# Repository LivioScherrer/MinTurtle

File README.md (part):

# EduBot V2

Firmware fuer einen Educational-Roboter auf **Seeed XIAO ESP32S3** mit zwei
NEMA8-Steppern (TMC2209), Farbsensor (TCS34725), Distanzsensor (VL53L0X),
NeoPixel-Ring, BLE-Steuerung und ESP-NOW-Multiplayer.

Zielgruppe der Web-UI ist Grundschule - alle Spiele laufen ueber Bloecke
(Wiederhole, Fahre, Drehe, Warte, Lies Farbe), die per Scratch-Logik
zusammengeklickt werden.

---

## Bauen und Flashen

```bash
pio run                 # kompilieren
pio run -t upload       # auf den Roboter flashen (COM11 in platformio.ini)
pio device monitor      # Serial-Log (115200 baud)
```

Ziel: `seeed_xiao_esp32s3`, Flash 3.3 MB (Stand 2026-10-10: 43,4 % belegt), RAM
327 KB (Stand 2026-10-10: 20,9 % belegt).

Zwei Web-Seiten, beide Single File, kein Build-Schritt. Sie sprechen denselben
BLE-Dienst an und werden direkt aus dem Browser geöffnet (Chromium-Browser
nötig, Web Bluetooth).

> **Achtung beim Verteilen:** `Edu_V2.html` ist keine Einzeldatei mehr. Die
> Schrift **Nunito** liegt selbst gehostet im Ordner `fonts/` daneben
> (2 × `.woff2` + `OFL-Nunito.txt`), damit alle Geräte — auch offline — genau
> gleich aussehen. Wird nur die `.html` kopiert, fällt die Seite still auf
> Comic Sans & Co. zurück. **Immer den ganzen Ordner kopieren.**

| Datei | Für wen | Inhalt |
|---|---|---|
| **`Edu_V2.html`** | **Schüler** | Alle Spiele, Freifahren, Code-Bausteine, Lernkarte. **Keine Diagnose**, keine Fehlermeldungen über unbekannte Befehle. |
| **`Edu_V2_dev.html`** | Entwickler | Kleine Konsole: Protokoll jeder gesendeten und empfangenen Zeile, geparste Werte (TMC, Geometrie, Tempo, Distanz, Freifahren-Kette), freier Befehlseingabe. |

Warum das getrennt ist: `handleCommand()` protokolliert jeden Befehl mit
`Serial.printf("[CMD] %s\n", …)`, und die Firmware antwortet auf Unbekanntes
mit `UNKNOWN:<befehl>`. Auf der Schülerseite wird das **nicht** angezeigt —
für ein Kind ist „Unbekannter Befehl: PROG:OLDRUN" eine tote Fehlermeldung, an
der es nichts zu tun hat, während der Roboter völlig normal läuft. Wer sehen
will, was wirklich ankommt, öffnet die Entwicklerseite.

> **Ein `UNKNOWN:` im Protokoll bedeutet fast immer:** der Browser hat eine
> **alte Kopie** der Web-Seite gecacht und sendet Befehle, die die aktuelle
> Firmware nicht mehr kennt. Abhilfe: Seite neu laden (Strg+F5). Die
> Entwicklerseite zeigt dann sofort, welcher Befehl es ist.

Beide Seiten brauchen die gleichen BLE-UUIDs (siehe `BLEManager.cpp` und den
Kopf beider HTML-Dateien).

---

## Hardware / Verdrahtung

### Motoren (TMC2209, STEP/DIR + UART)

Beide Treiber hängen an einem **gemeinsamen Single-Wire-UART-Bus**.
VIO = 3V3, VM = Motorspannung (ohne VM antwortet der Treiber nicht).

> **Diese Tabelle ist die am Fahrroboter geprüfte IST-Verdrahtung (2026-09).**
> Sie stimmt mit `src/Motor.h` überein. Eine frühere Fassung dieses README
> stand hier spiegelverkehrt (U2/J1 als „links") — das war die Verdrahtung,
> bei der jede Drehung auf der Stelle in die falsche Richtung lief. Wer
> `Motor.h` nicht glaubt, sollte `PIN_STEP_*`/`TMC_ADDR_*` dort nachsehen,
> nicht hier.

| Signal | GPIO | Hinweis |
|---|---|---|
| STEP links | 2 (D1) | U4 / J5, TMC-Adresse `0b01` |
| DIR links  | 1 (D0) | |
| STEP rechts | 7 (D8) | U2 / J1, TMC-Adresse `0b00` |
| DIR rechts  | 3 (D2) | STEP/DIR auf dem PCB gedreht, hier kompensiert |
| EN (beide)  | 4    | LOW aktiv |
| UART TX     | 43 (D6) | über 1 kΩ (R9) an das PDN-Netz |
| UART RX     | 44 (D7) | direkt am PDN-Netz |

Adressen: links `0b01` (MS1=3V3, MS2=GND), rechts `0b00` (MS1=GND, MS2=GND).
R_Sense auf dem PCB: 560 mΩ.

> **Achtung, D8 ist auf dem ESP32-S3 GPIO 7** (auf dem klassischen XIAO
> ESP32 war D8 = GPIO 8). `PIN_STEP_R 7 // D8` in `Motor.h` ist also korrekt
> und sieht nur falsch aus — bitte nicht auf 8 „korrigieren“.

#### Drehrichtung (`LEFT_MOTOR_SIGN` / `RIGHT_MOTOR_SIGN`)

Die Drehrichtung steckt in **zwei Konstanten** am Anfang von `src/Config.h`:

```cpp
constexpr int8_t LEFT_MOTOR_SIGN  = +1;   // links  (U4/J5, D0/D1)
constexpr int8_t RIGHT_MOTOR_SIGN = -1;   // rechts (U2/J1, D2/D8)
```

Feste Konstanten, **bewusst keine NVS-Werte und keine Web-UI-Einstellung.**
Ein einmal falsch gespeicherter Wert würde jeden späteren korrigierten
Default bei jedem Build überschreiben – die Quelle soll die einzige
Wahrheit bleiben.

Weiter wichtig:

- Beide Werte werden **an jeder Stelle angewendet** – `setMotorSpeed()`
  multipliziert intern mit dem Vorzeichen, die zehn `prepPositionMove()`-
  Aufrufer ebenfalls. Der Faktor wirkt also **genach einmal**. Wer ihn in
  `Motor.cpp` nochmals umkehrt, dreht beide Motoren wieder um.
- **Die beiden Werte müssen unterschiedlich sein.** Sind sie gleich, drehen
  beide Räder gleichsinnig und der Roboter dreht sich auf der Stelle statt
  zu fahren. Ein `static_assert` in `Config.h` bricht den Build in dem
  Fall ab – lieber kein Build als ein Roboter, der im Kreis fährt.

**Symptome falscher Werte** (Roboter frei auf dem Tisch, `W` gedrückt):

| Beobachtung | Ursache |
|---|---|
| dreht sich auf der Stelle | beide Werte gleich (Build bricht ab) |
| fährt rückwärts | Werte unterschiedlich, aber beide umgekehrt zur nötigen Polarität |
| fährt geradeaus, dreht auf der Stelle in die falsche Richtung | Fahrzeichen stimmt, aber `gameTurnSteps()`-Logik prüfen |

#### Modus-Automatik: `TPWMTHRS` und StallGuard

Zwei Register, die früher nicht gesetzt wurden und jetzt in `configureOne()`
mitlaufen (`src/Motor.h`):

- **`TPWMTHRS` = 601** → Umschaltung auf SpreadCycle ab 60 mm/s. Vorher stand
  hier `TPWMTHRS(0)`, und `0` bedeutet laut Datenblatt *Disabled*: der Treiber
  blieb bei **jeder** Geschwindigkeit in StealthChop, also auch dort, wo
  StealthChop die wenigste Drehmomentreserve hat. Der Wert ist unabhängig von
  der Microstep-Zahl (er bezieht sich immer auf 1/256 Schritt), ein Wert reicht
  für alle Microstep-Einstellungen.
- **`TCOOLTHRS` = 2402** → StallGuard erst ab 15 mm/s auswerten. Unterhalb
  dieser Geschwindigkeit ist er nicht verlässlich.
- **`SGTHRS` = 100** → Stall bei `SG_RESULT ≤ 200`. Der Wert ist
  anwendungsabhängig, das Datenblatt gibt keine Vorgabe. **Nichts in der
  Firmware handelt darauf** — er wird nur gelesen und zusammen mit beiden
  `SG_RESULT`-Werten gemeldet. Ein zu niedriger Wert kann deshalb keinen
  Schaden anrichten, und der echte Wert ist am Roboter ablesbar.

Die Herleitung der Registerwerte steht ausgeschrieben bei
`TMC_SPREADCYCLE_AB_MM_S` in `Motor.h`: `Registerwert = 2^24 · Radumfang /
(51200 · v[mm/s])`, gegengeprüft an der OTP-Tabelle des Herstellers.

### I2C-Sensoren

| Sensor | Adresse | Pins |
|---|---|---|
| TCS34725 (Farbe) | 0x29 | SDA=GPIO5, SCL=GPIO6 |
| VL53L0X (Distanz) | 0x30 (nach Umzug) | gleicher Bus |

> **Reihenfolge zwingend:** `distSetup()` **vor** `colorSetup()`.
> Beide Sensoren haben Default-Adresse 0x29; der VL53L0X wird beim Boot
> auf 0x30 umadressiert, damit sie koexistieren koennen. Die Umadressierung
> ist fluechtig und wird bei jedem Boot erneut durchgefuehrt.
>
> **Wichtig:** Sind beide Sensoren gleichzeitig physisch am Bus, reicht die
> Reihenfolge allein nicht - ein auch noch nicht konfigurierter TCS34725
> antwortet bereits auf 0x29 und verfaelscht damit die NVM-Reads des
> VL53L0X. Details und Loesungswege siehe
> [VL53L0X und der Adresskonflikt](#vl53l0x-und-der-adresskonflikt-wichtigste-falle-im-projekt).

### Weitere Peripherie

- **NeoPixel-Ring** (LED-Strip, 7 LEDs, GPIO 8) - Statusanzeige, siehe unten
- **Motor-Referenz**: NEMA8 8HS11-0204S (0,2 A Nennstrom, 24 Ω, 8 mH)

### LED-Statusanzeige (NeoPixel-Ring)

Der Ring ist die Statusanzeige des Roboters. `LedStrip.cpp` ist eine
Muster-Engine: `ledStripShowXxx()` waehlt nur ein Muster, `ledStripTick()`
zeichnet es zeitbasiert (max. 25 Bilder/s, nicht blockierend). Die
Main-Loop waehlt in `ledPatternUpdate()` **ein** Muster nach Prioritaet,
Alarm (Not-Aus) und Ergebnisblitze uebersteuern die Kette intern fuer eine
kurze Haltezeit.

| Situation | Anzeige |
|---|---|
| Boot | Pixel-Selbsttest (jede LED einmal weiss), danach Sensor-Selbsttest: 2x gruen = beide Sensoren OK; linker Teil magenta blinkend = Farbsensor fehlt, rechter Teil rot blinkend = Distanzsensor fehlt |
| Ruhezustand, App verbunden | blaues Atmen |
| Ruhezustand, keine App | oranges Atmen (wartet auf Verbindung) |
| Slalom gepaart (Gegner verbunden, Start noch offen) | cyanfarbenes Atmen |
| Freifahren | gruenes Lauflicht in Fahrtrichtung; Drehen auf der Stelle: zwei Punkte wandern nach aussen |
| Quiz (Korrigieren) | Fortschrittsbalken: gruen solange alles stimmt, sonst rot; waehrend des Farblesens bleibt der Ring dunkel; Ende: gruener bzw. roter Blitz |
| Memory | Sequenz-Ansicht: violettes Lauflicht; Eingabe: gruener Fortschrittsbalken, der naechste Punkt blinkt |
| Linienfolger | gruener Scanner (Linie erkannt), oranges Blinken (Suche), rotes langsames Blinken (Hindernis) |
| Rennen | gelbes Lauflicht |
| Slalom Bauphase | Zielfarbe pulsiert |
| Slalom Countdown | Startampel: erst 2, dann 4, dann 6 rote LEDs, bei GO die ganze Reihe gruen |
| Slalom entschieden | Sieg = Regenbogen, Niederlage = rotes Atmen |
| Not-Aus (`STOP`) | rotes Doppelblinken, 3 s |
| Tischkante ausgeloest (gesperrt bis Boden/`EDGE:RESET`) | alle LEDs rot blinkend |

Zwei Regeln sind bewusst so gewaehlt:

1. **Waehrend Farbmessungen bleibt der Ring dunkel** (Slalom-Rennen,
   Quiz-Lesephase, ausgefuehrte Programme). Eigenes LED-Licht koennte sonst
   als Farbe auf dem Boden erkannt werden. Der Not-Aus-Alarm und das
   Kanten-Rot blinken trotzdem - Sicherheit geht vor Messgenauigkeit.
2. **Der S-Block** (`Licht`-Baustein) nutzt dieselbe Anzeige: Slots 0-3 zeigen
   die Zielfarbe, Slot 4/5 die Distanz-Bedeutung NAH (dunkelrot) / FREI
   (dunkelgruen), Slot 6 schaltet aus.

### Code-Bausteine (Blockprogrammierung)

Die Web-UI baut das Programm als kurzen String (`PROG:SET:<enc>`). Die
Bausteine sind nach **Aufgabe** gruppiert, nicht nach Technik — genau diese
technische Gruppierung war es, an der man nicht durchblickte.

| Reiter | Bausteine | Kodierung |
|---|---|---|
| Fahren | vorwärts/rückwärts cm, drehe links/rechts ° | `F20` `B15` `L90` `R90` |
| **Fahre bis** | **fahre bis [Farbe]**, **fahre bis Abstand [mm]** | **`P0`**…`P5` **`D150`** |
| Warten | warte s, warte bis [Farbe], warte bis Abstand mm | `W2` `V1` `X150` |
| Wiederholen | wiederhole n mal, wiederhole bis [Farbe] | `U4(...)` `C2(...)` |
| Genau fahren | vorwärts/rückwärts mm | `M45` `N45` |
| Sonstiges | Licht, Stopp, kurze Pause, warte bis frei mm | `S1` `Q` `Z5` `G300` |

Slot 0-3 sind ROT/GELB/GRÜN/BLAU, Slot 4 = Hindernis erkannt, Slot 5 = Weg frei.
Der Farb-Chip im Baustein wird durch Anklicken weitergeschaltet.

**„Fahre bis …" läuft für alle drei Fälle über eine Routine**
(`progDriveUntil()`): eine einzige Rampe, dann durchgehende Fahrt mit einer
Prüfung alle ~10 ms. Vorher gab es zwei getrennte Wege, und der Abstands-Baustein
fuhr in 10-mm-Etappen mit jeweils eigener Rampe — bei 150 ms Anfahrzeit kostet
jede Etappe mehr Zeit im Anfahren als im Fahren.

Drei Dinge, die dabei bewusst so gelöst sind:

1. **Flanken-Logik bei Farben.** Steht der Roboter schon auf der Zielfarbe,
   hält er nicht sofort, sondern erst bei der *nächsten* Farbe. Sonst wäre
   „fahre bis Rot" auf rotem Boden ein Baustein ohne Wirkung.
2. **Zwei Sicherheitsnetze**, unabhängig voneinander: höchstens 1,5 m und
   höchstens 20 s. Ohne sie fährt der Roboter bei blindem Sensor endlos weiter.
3. **Kein zusätzlicher Halt auf der Hindernis-Schwelle** beim Abstands-Baustein.
   Die Schwelle steht an anderer Stelle und würde den Baustein beenden, bevor
   sein eigener Wert erreicht ist — der Roboter hielte an, ohne dass klar wäre,
   warum.

Der alte Weg „F/B mit angehängtem E-Wertblock" (`FE2`, im Parser gleich auf
`OP_DRIVE_UNTIL` umgewandelt) wird weiterhin gelesen und läuft jetzt über
dieselbe Routine. Der E-Wertblock selbst steht nicht mehr in der Palette: für
„bis Farbe" gibt es mit `P` genau einen Weg, und zwei Wege für dieselbe Sache
waren einer zu viel.

### Drift: „Software oder Hardware?" — die Messgröße dafür

Jedes Freifahren-Manöver (`driveUpdate()`) gibt am Ende automatisch eine Zeile
aus:

```
[DRV] Fahrt beendet: Schritte L=16862 R=16861 (Diff 1)
[DRV]   Zaehler praktisch gleich -> Drift ist MECHANISCH
```

Die Zähler sind `AccelStepper::currentPosition()` — sie zählen **jeden
erzeugten Puls**, unabhängig davon, ob das Rad rollt. Damit ist die Frage
entscheidbar statt vermutbar:

| Befund | Bedeutung |
|---|---|
| Zähler gleich (Diff ≤ 2), Roboter driftet sichtbar | **mechanisch**: Rad steht schief, Getriebespiel, Reibung, Spannung im Chassis |
| Zähler unterscheiden sich | **Software**: die Räder werden ungleich angesteuert (zuerst `leftSign`/`rightSign`, dann der Puls-Task) |
| Zähler gleich *und* Strecke stimmt nicht | Zeitbasis: `MOTOR_TICK_US`, `MAX_DRIVE_STEPS_S` |

Gleiche Zahlen stehen auch in `DRV?` (`pos=<L>/<R> d=<Diff>`) und auf der
Diagnose-Seite. Reine Diagnose — am Fahrverhalten ändert sich nichts.

### TMC2209: Registerkarte nicht aus der Bibliothek übernehmen

**Das ist die wichtigste Falle im ganzen Projekt.** TMCStepper adressiert den
TMC2209 mit der Registerkarte des **TMC2130**. Dort liegt `CHOPCONF` auf
**0x06** — beim TMC2209 ist 0x06 aber **IOIN** und damit nur lesbar.

Gemessen auf dem Roboter (2026-10, COM9): `toff`, `mres`, `intpol`, `pwm_autoscale`,
Strom und Hold waren nie angekommen. Stattdessen liefen beide Treiber auf
Auslieferungswerte — mit **IRUN = 31 (voller Strom)**, also rund **396 mA RMS**
bei 560 mΩ Fühlerwiderstand, für einen Motor mit **0,2 A Nennstrom**.

| Register | TMC2209 (UART) | TMC2130 (was TMCStepper nutzt) |
|---|---|---|
| `GCONF` | 0x00 | 0x00 ✔ zufällig gleich |
| `CHOPCONF` | **0x08** | 0x06 ✘ = IOIN, nur lesbar |
| `IHOLD_IRUN` (Strom) | **0x10** | — |
| `TPOWER` | 0x11 | 0x19 ✘ |
| `TSTEP` / `TPWMTHRS` / `TCOOLTHRS` | 0x12 / 0x13 / 0x14 | 0x13 / 0x15 / 0x16 ✘ |
| `VACTUAL` | 0x22 | ✔ |
| `SGTHRS` / `SG_RESULT` | 0x40 / 0x41 | ✔ |

Deshalb schreibt `configureOne()` **alle Register selbst** über
`tmcWriteChecked()` mit den Adressen aus dem Datenblatt.

**Zwei Fallen, die zusammen sehr viel Zeit gekostet haben:**

1. **Nur-schreibbare Register kann man nicht zurücklesen.** `CHOPCONF`,
   `IHOLD_IRUN`, `TPOWER`, `TPWMTHRS`, `TCOOLTHRS`, `SGTHRS` und `NODECONF`
   sind im Datenblatt mit `W` gekennzeichnet. Ein Readback liefert dort
   konstant 0 — daraus entstand die Fehldiagnose „die Schwellen kommen nicht
   an". **Belegbar sind sie nur über `IFCNT`:** „This register becomes
   incremented with each successful UART interface write access." Nach der
   Konfiguration muss dieser Zähler um die Anzahl der Schreibzugriffe
   gewachsen sein. Genau das prüft `configureOne()` jetzt.
2. **`ENN` ist auch ein Reset.** Das Datenblatt (5.5.1): „Indicates that the
   IC has been reset since the last read access to GSTAT. **All registers
   have been cleared to reset values.**" Der Auto-Standby schaltet nach 3 s auf
   EN=HIGH und löscht damit jedes Register — ohne jede Fehlermeldung.
   `tmcEnable()` konfiguriert deshalb neu, sobald der Treiber wieder
   eingeschaltet wird.

**MS1/MS2 tragen doppelte Funktion:** Sie wählen die UART-Adresse *und* — solange
`mstep_reg_select = 0` — die Microstep-Auflösung (Datenblatt 4.3 und 5.5.1).
Diese Platine nutzt sie für die Adresse (links `0b01`, rechts `0b00`); ohne
`mstep_reg_select` wären die Räder auf 128 bzw. 256 Microsteps gelaufen,
während die Firmware für beide 32 rechnet.

**Strom:** `IRUN` (Bit 12..8) und `IHOLD` (Bit 4..0) des Registers 0x10 sind
Strom-*Skalen* 0..31 (0 = 1/32, 31 = 32/32). Die Widerstände und VREF legen die
**Obergrenze** fest (~396 mA bei 560 mΩ und `vsense = 0`), `IRUN` skaliert nur
darunter. Für die festen 200 mA folgt `IRUN = 16` → **210 mA**. Das Datenblatt
empfiehlt ausdrücklich „IRUN is 16 to 31 for best microstep performance" —
darunter wird deshalb gekappt.

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
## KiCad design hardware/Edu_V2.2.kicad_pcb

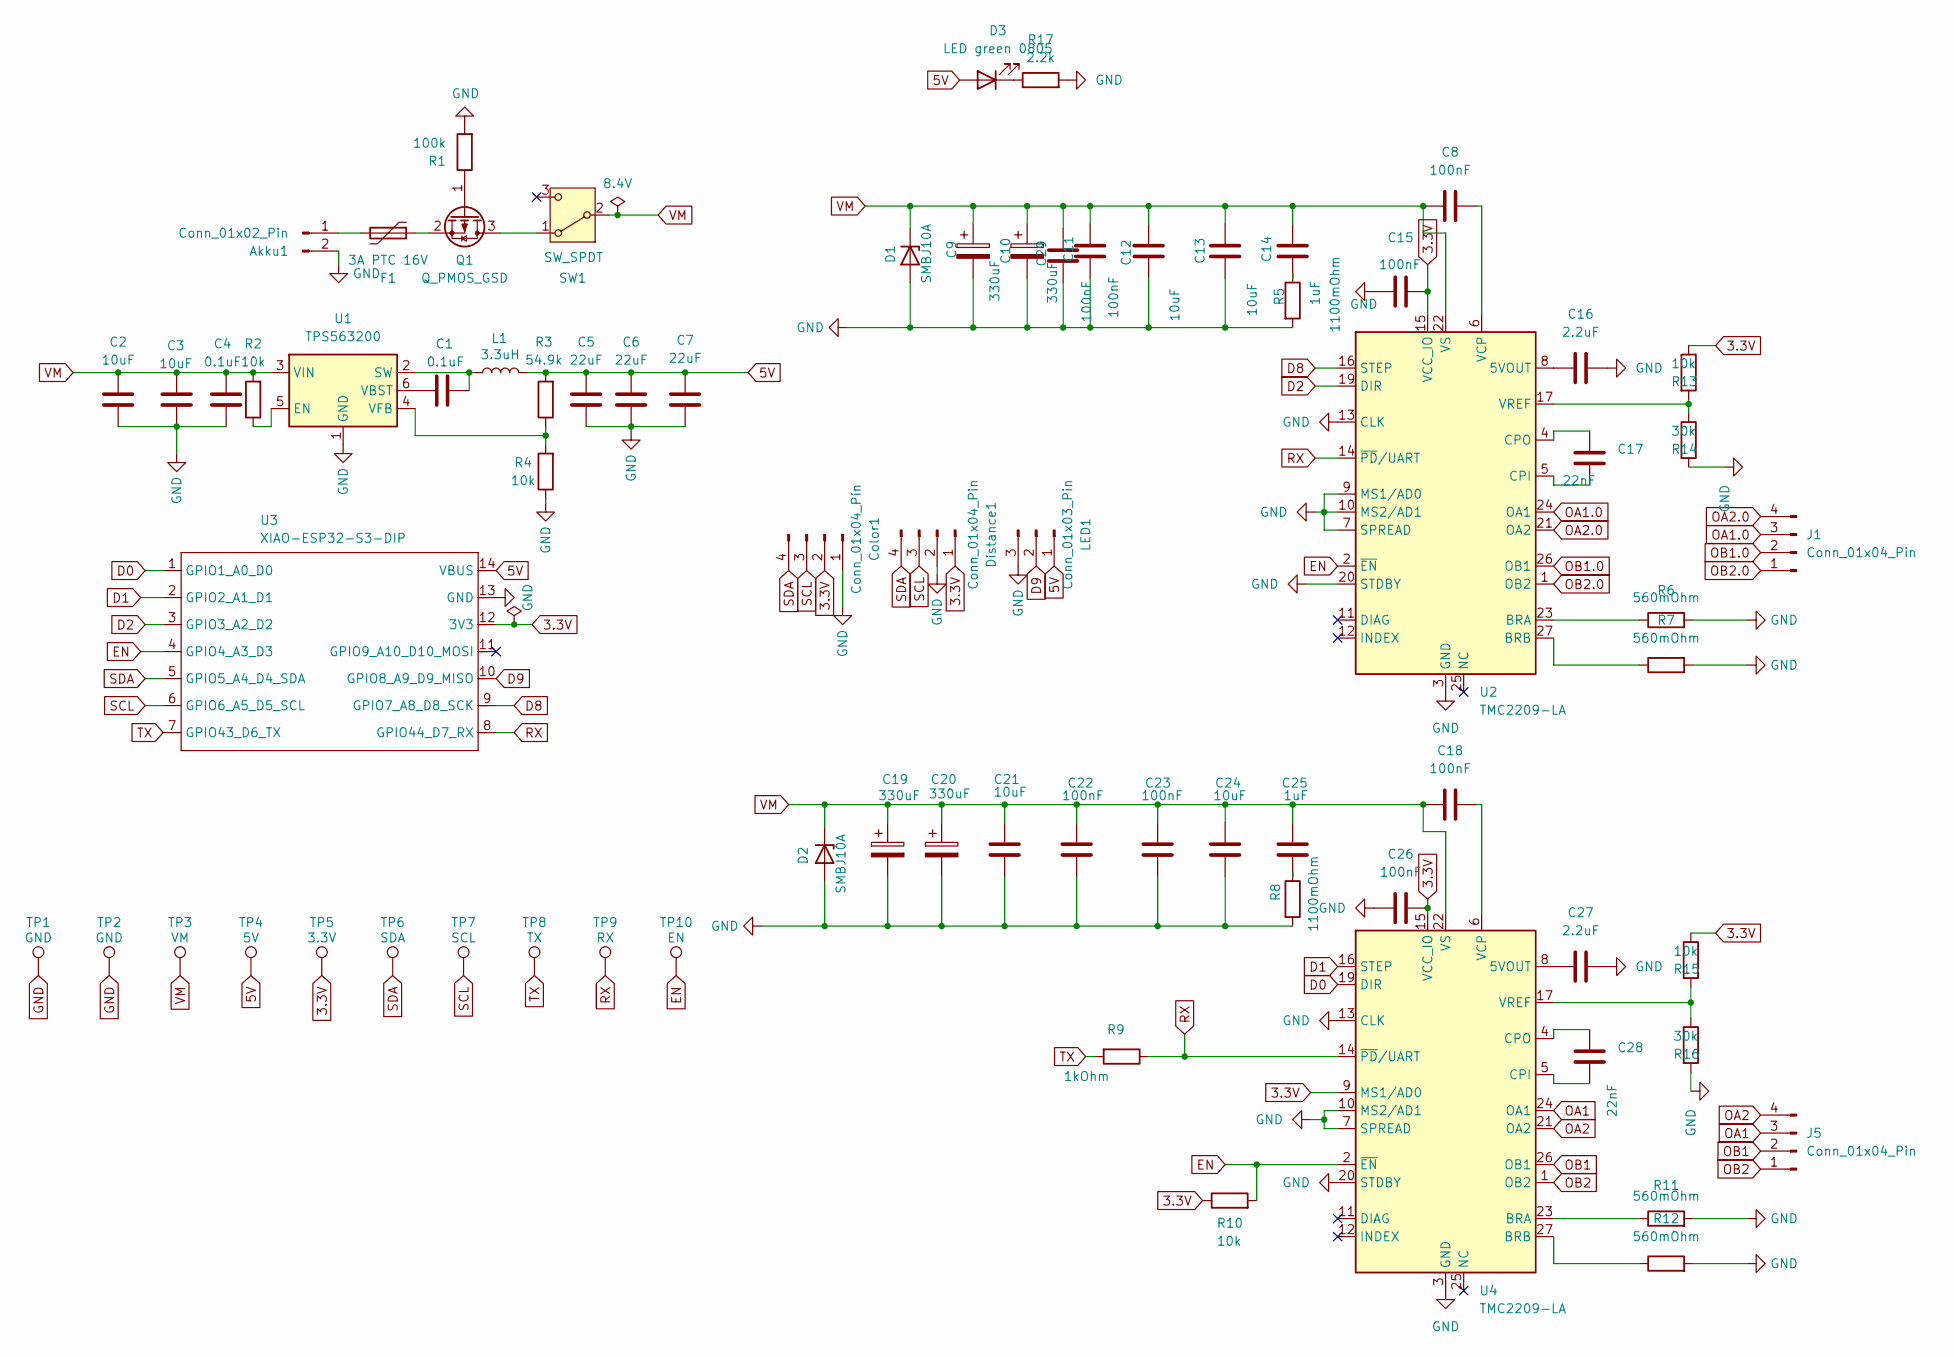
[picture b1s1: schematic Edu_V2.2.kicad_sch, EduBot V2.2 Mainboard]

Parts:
Akku1: Conn_01x02_Pin; PinHeader_1x02_P2.54mm_Vertical; MPN PZ254V-11-02P
C1, C4: 0.1uF; C_0603_1608Metric; MPN CC0603KRX7R9BB104; LCSC C14663
C2, C3: 10uF; C_0805_2012Metric; MPN CL21A106KAYNNNE; LCSC C15850
C5, C6, C7: 22uF; C_0805_2012Metric; MPN CL21A226MAQNNNE; LCSC C45783
C8, C11, C15, C18, C22, C23, C26, C29: 100nF; C_0603_1608Metric; MPN CC0603KRX7R9BB104; LCSC C14663
C9, C10, C19, C20: 330uF; CP_Elec_6.3x7.7; MPN GVM1E331M0607; LCSC C2980171
C12, C13, C21, C24: 10uF; C_2220_5750Metric; MPN FS55X106K500EGG; LCSC C153034
C14, C25: 1uF; C_1210_3225Metric; MPN CL32B105KBHNNNE; LCSC C40708
C16, C27: 2.2uF; C_0603_1608Metric; MPN CC0603KRX5R8BB225; LCSC C309478
C17, C28: 22nF; C_0805_2012Metric; MPN CL21B223KBANNNC; LCSC C1729
Color1: Conn_01x04_Pin; JST_SH_BM04B-SRSS-TB_1x04-1MP_P1.00mm_Vertical; MPN BM04B-SRSS-TB(LF)(SN); LCSC C160390
D1, D2: SMBJ10A; D_SMB; MPN SMBJ10A; LCSC C353406
D3: LED green 0805; LED_0805_2012Metric; MPN KT-0805G; LCSC C2297
Distance1: Conn_01x04_Pin; JST_SH_BM04B-SRSS-TB_1x04-1MP_P1.00mm_Vertical; MPN BM04B-SRSS-TB(LF)(SN); LCSC C160390
F1: 3A PTC 16V; Fuse_1210_3225Metric_Pad1.42x2.65mm_HandSolder; MPN 1210L300/16WR; LCSC C22379948
J1, J5: Conn_01x04_Pin; JST_SH_BM04B-SRSS-TB_1x04-1MP_P1.00mm_Vertical; MPN BM04B-SRSS-TB(LF)(SN); LCSC C160390
L1: 3.3uH; L_1210_3225Metric; MPN DFE322512F-3R3M=P2; LCSC C3221010
LED1: Conn_01x03_Pin; JST_GH_BM03B-GHS-TBT_1x03-1MP_P1.25mm_Vertical; MPN BM03B-GHS-TBT(LF)(SN); LCSC C161691
Q1: Q_PMOS_GSD; SOT-23; MPN AO3401A; LCSC C15127
R1: 100k; R_0805_2012Metric; MPN 0805W8F1003T5E; LCSC C149504
R2, R4, R13, R15: 10k; R_0603_1608Metric; MPN 0603WAF1002T5E; LCSC C25804
R3: 54.9k; R_0603_1608Metric; MPN 0603WAF5492T5E; LCSC C23077
R5, R8: 1100mOhm; R_0603_1608Metric; MPN RCT031R1JLF; LCSC C177315
R6, R7, R11, R12: 560mOhm; R_2010_5025Metric; MPN CR2010FR560E04R; LCSC C165409
R9: 1kOhm; R_0805_2012Metric; MPN 0805W8F1001T5E; LCSC C17513
R10: 10k; R_0805_2012Metric; MPN 0805W8F1002T5E; LCSC C17414
R14, R16: 30k; R_0603_1608Metric; MPN 0603WAF3002T5E; LCSC C22984
R17: 2.2k; R_0603_1608Metric; MPN 0603WAF2201T5E; LCSC C4190
SW1: SW_SPDT; SW_Slide-03_Wuerth-WS-SLTV_10x2.5x6.4_P2.54mm
TP1, TP2: GND; TestPoint_Pad_D1.5mm
TP3: VM; TestPoint_Pad_D1.5mm
TP4: 5V; TestPoint_Pad_D1.5mm
TP5: 3.3V; TestPoint_Pad_D1.5mm
TP6: SDA; TestPoint_Pad_D1.5mm
TP7: SCL; TestPoint_Pad_D1.5mm
TP8: TX; TestPoint_Pad_D1.5mm
TP9: RX; TestPoint_Pad_D1.5mm
TP10: EN; TestPoint_Pad_D1.5mm
U1: TPS563200; SOT-23-6; MPN TPS563200DDCR; LCSC C97253
U2, U4: TMC2209-LA; VQFN-28-1EP_5x5mm_P0.5mm_EP3.7x3.7mm_ThermalVias; MPN TMC2209-LA-T; LCSC C2150710
U3: XIAO-ESP32-S3-DIP

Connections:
3.3V: C15.2, C26.2, Color1.2, Distance1.1, R10.1, R13.1, R15.1, TP5.1, U2.15 (VCC_IO), U3.12 (3V3), U4.9 (MS1/AD0), U4.15 (VCC_IO)
5V: C5.2, C6.2, C7.2, D3.2 (A), L1.2, LED1.1, R3.2, TP4.1, U3.14 (VBUS)
D0: U3.1 (GPIO1_A0_D0), U4.19 (DIR)
D1: U3.2 (GPIO2_A1_D1), U4.16 (STEP)
D2: U2.19 (DIR), U3.3 (GPIO3_A2_D2)
D8: U2.16 (STEP), U3.9 (GPIO7_A8_D8_SCK)
D9: LED1.2, U3.10 (GPIO8_A9_D9_MISO)
EN: R10.2, TP10.1, U2.2 (~EN), U3.4 (GPIO4_A3_D3), U4.2 (~EN)
GND: Akku1.2 (GND), C2.1, C3.1, C4.1, C5.1, C6.1, C7.1, C9.2, C10.2, C11.1, C12.1, C13.1, C15.1, C16.1, C19.2, C20.2, C21.1, C22.1, C23.1, C24.1, C26.1, C27.1, C29.1, Color1.1, D1.2 (A), D2.2 (A), Distance1.2, LED1.3, R1.2, R4.1, R5.2, R6.2, R7.2, R8.2, R11.2, R12.2, R14.2, R16.2, R17.2, TP1.1, TP2.1, U1.1 (GND), U2.3 (GND), U2.7 (SPREAD), U2.9 (MS1/AD0), U2.10 (MS2/AD1), U2.13 (CLK), U2.18 (GND), U2.20 (STDBY), U2.29 (GND), U3.13 (GND), U4.3 (GND), U4.7 (SPREAD), U4.10 (MS2/AD1), U4.13 (CLK), U4.18 (GND), U4.20 (STDBY), U4.29 (GND)
unnamed: Akku1.1 (VCC), F1.2
unnamed: C14.1, R5.1
unnamed: C25.1, R8.1
unnamed: D3.1 (K), R17.1
unnamed: Q1.3 (D), SW1.1 (A)
unnamed: Q1.1 (G), R1.1
unnamed: F1.1, Q1.2 (S)
unnamed: R2.1, U1.5 (EN)
unnamed: C1.2, L1.1, U1.2 (SW)
unnamed: C1.1, U1.6 (VBST)
unnamed: R3.1, R4.2, U1.4 (VFB)
unnamed: C16.2, U2.8 (5VOUT)
unnamed: R6.1, U2.23 (BRA)
unnamed: R7.1, U2.27 (BRB)
unnamed: C17.1, U2.5 (CPI)
unnamed: C17.2, U2.4 (CPO)
unnamed: C8.2, U2.6 (VCP)
unnamed: R13.2, R14.1, U2.17 (VREF)
unnamed: C27.2, U4.8 (5VOUT)
unnamed: R11.1, U4.23 (BRA)
unnamed: R12.1, U4.27 (BRB)
unnamed: C28.1, U4.5 (CPI)
unnamed: C28.2, U4.4 (CPO)
unnamed: C18.2, U4.6 (VCP)
unnamed: R15.2, R16.1, U4.17 (VREF)
OA1: J5.3, U4.24 (OA1)
OA1.0: J1.3, U2.24 (OA1)
OA2: J5.4, U4.21 (OA2)
OA2.0: J1.4, U2.21 (OA2)
OB1: J5.2, U4.26 (OB1)
OB1.0: J1.2, U2.26 (OB1)
OB2: J5.1, U4.1 (OB2)
OB2.0: J1.1, U2.1 (OB2)
RX: R9.1, TP9.1, U2.14 (~PD/UART), U3.8 (GPIO44_D7_RX), U4.14 (~PD/UART)
SCL: Color1.3, Distance1.3, TP7.1, U3.6 (GPIO6_A5_D5_SCL)
SDA: Color1.4, Distance1.4, TP6.1, U3.5 (GPIO5_A4_D4_SDA)
TX: R9.2, TP8.1, U3.7 (GPIO43_D6_TX)
VM: C2.2, C3.2, C4.2, C8.1, C9.1, C10.1, C11.2, C12.2, C13.2, C14.2, C18.1, C19.1, C20.1, C21.2, C22.2, C23.2, C24.2, C25.2, C29.2, D1.1 (K), D2.1 (K), R2.2, SW1.2 (B), TP3.1, U1.3 (VIN), U2.22 (VS), U2.28 (VS), U4.22 (VS), U4.28 (VS)

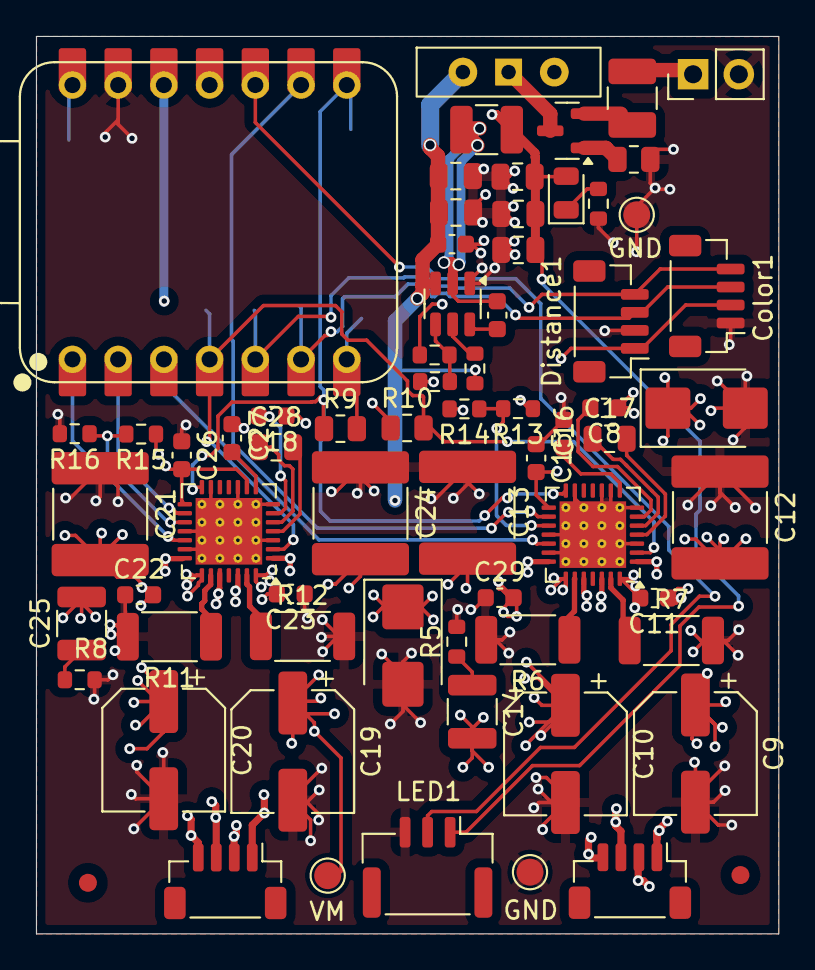
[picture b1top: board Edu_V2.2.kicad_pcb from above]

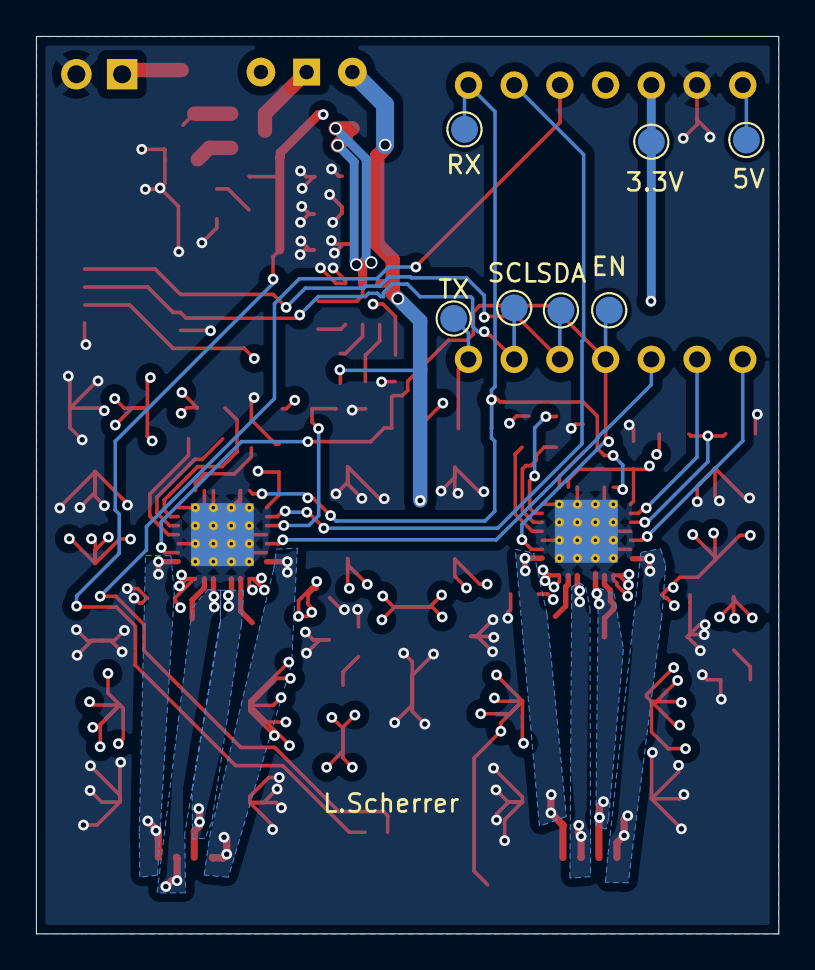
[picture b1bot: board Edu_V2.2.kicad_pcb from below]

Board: 4 copper layers, 41.2 x 49.9 mm, 75 parts (7 on the bottom side), 47 nets.

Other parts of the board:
FID1, FID2: Fiducial_1mm_Mask2mm

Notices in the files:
hardware/Edu_V2.2.kicad_pcb:
Open-Source-Hardware unter CERN-OHL-P-2.0
